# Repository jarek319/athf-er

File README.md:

# athf-er
Blinking LED welcome sign

I made this sign to welcome people to my house warming party. The lights alternate between his hand being down and flying the bird.

I was never comfortable in Inkscape, so I made the acrylic laser cutout design using Eagle. This helped me get exact sizing for the cutouts and an easily mesaureable layout, perfect for pixel stuff.

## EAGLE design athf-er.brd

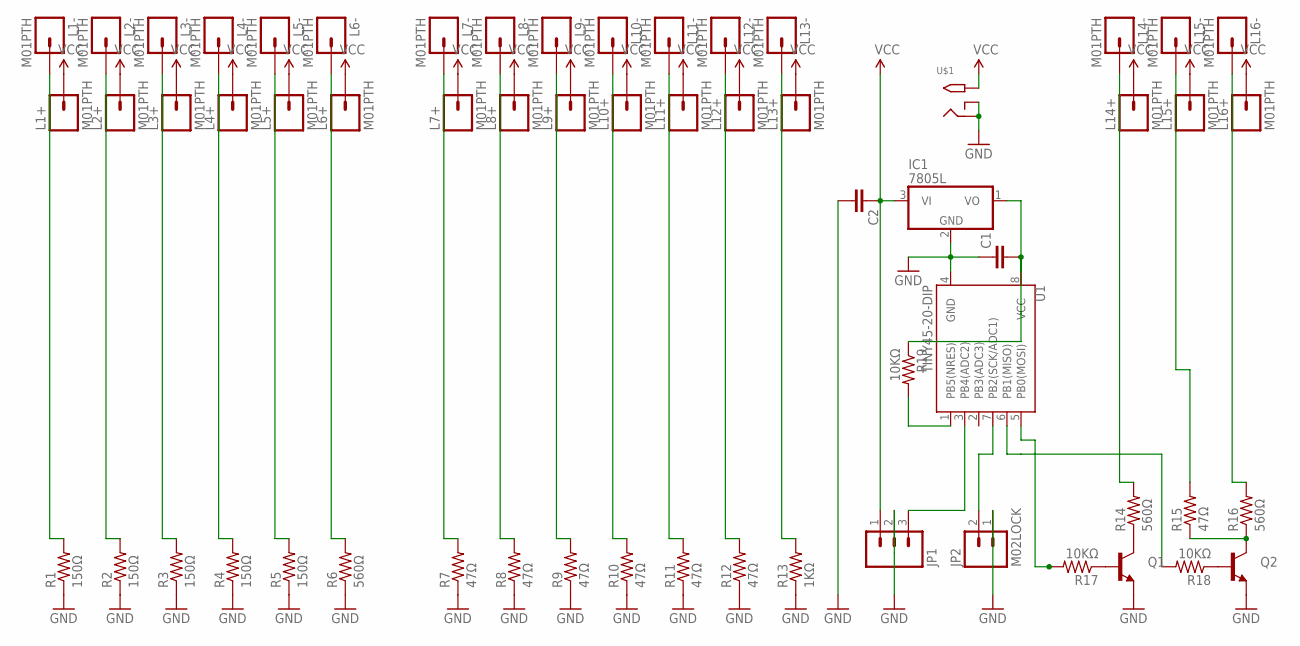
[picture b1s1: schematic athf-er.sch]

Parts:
C1, C2: CAPEZ; CAP-PTH-SMALLEZ
IC1: 7805L; TO92
JP1: M03LOCK; 1X03_LOCK
JP2: M02LOCK; 1X02_LOCK
L1+, L1-, L2+, L2-, L3+, L3-, L4+, L4-, L5+, L5-, L6+, L6-, L7+, L7-, L8+, L8-, L9+, L9-, L10+, L10-, L11+, L11-, L12+, L12-, L13+, L13-, L14+, L14-, L15+, L15-, L16+, L16-: M01PTH; 1X01
Q1, Q2: TRANSISTOR_NPNTO92; TO-92
R1, R2, R3, R4, R5: 150Ω; AXIAL-0.3EZ
R6, R14, R16: 560Ω; AXIAL-0.3EZ
R7, R8, R9, R10, R11, R12, R15: 47Ω; AXIAL-0.3EZ
R13: 1KΩ; AXIAL-0.3EZ
R17, R18, R19: 10KΩ; AXIAL-0.3EZ
U1: TINY45-20-DIP; DIP08
U$1: 2.1MMJACKTHM; PJ-102A

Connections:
GND: C1.1, C2.2, IC1.2 (GND), JP1.2, JP2.1, Q1.1 (E), Q2.1 (E), R1.P$1 (1), R2.P$1 (1), R3.P$1 (1), R4.P$1 (1), R5.P$1 (1), R6.P$1 (1), R7.P$1 (1), R8.P$1 (1), R9.P$1 (1), R10.P$1 (1), R11.P$1 (1), R12.P$1 (1), R13.P$1 (1), U1.4 (GND), U$1.RING, U$1.RING_SW
unnamed: L1-.1, R1.P$2 (2)
unnamed: L2-.1, R2.P$2 (2)
unnamed: L3-.1, R3.P$2 (2)
unnamed: L4-.1, R4.P$2 (2)
unnamed: L5-.1, R5.P$2 (2)
unnamed: L6-.1, R6.P$2 (2)
unnamed: L7-.1, R7.P$2 (2)
unnamed: L8-.1, R8.P$2 (2)
unnamed: L9-.1, R9.P$2 (2)
unnamed: L10-.1, R10.P$2 (2)
unnamed: L11-.1, R11.P$2 (2)
unnamed: L12-.1, R12.P$2 (2)
unnamed: L13-.1, R13.P$2 (2)
unnamed: L14-.1, R14.P$2 (2)
unnamed: L16-.1, R16.P$2 (2)
unnamed: L15-.1, R15.P$2 (2)
unnamed: JP2.2, U1.7 (PB2(SCK/ADC1))
unnamed: Q2.3 (C), R15.P$1 (1), R16.P$1 (1)
unnamed: Q1.2 (B), R17.P$1 (1)
unnamed: Q1.3 (C), R14.P$1 (1)
unnamed: Q2.2 (B), R18.P$1 (1)
unnamed: JP1.3, U1.3 (PB4(ADC2))
unnamed: C1.2, IC1.1 (VO), R19.P$1 (1), U1.8 (VCC)
unnamed: R18.P$2 (2), U1.6 (PB1(MISO))
unnamed: R19.P$2 (2), U1.1 (PB5(NRES))
unnamed: R17.P$2 (2), U1.5 (PB0(MOSI))
VCC: C2.1, IC1.3 (VI), JP1.1, L1+.1, L2+.1, L3+.1, L4+.1, L5+.1, L6+.1, L7+.1, L8+.1, L9+.1, L10+.1, L11+.1, L12+.1, L13+.1, L14+.1, L15+.1, L16+.1, U$1.TIP

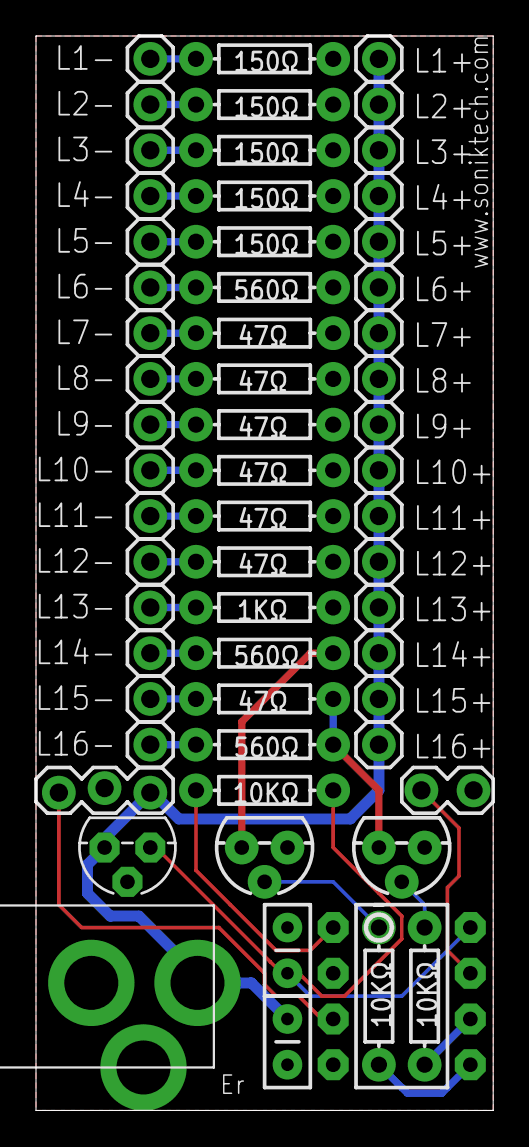
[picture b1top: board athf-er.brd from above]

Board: 2 copper layers, 25.4 x 59.7 mm, 60 parts (0 on the bottom side), 28 nets.

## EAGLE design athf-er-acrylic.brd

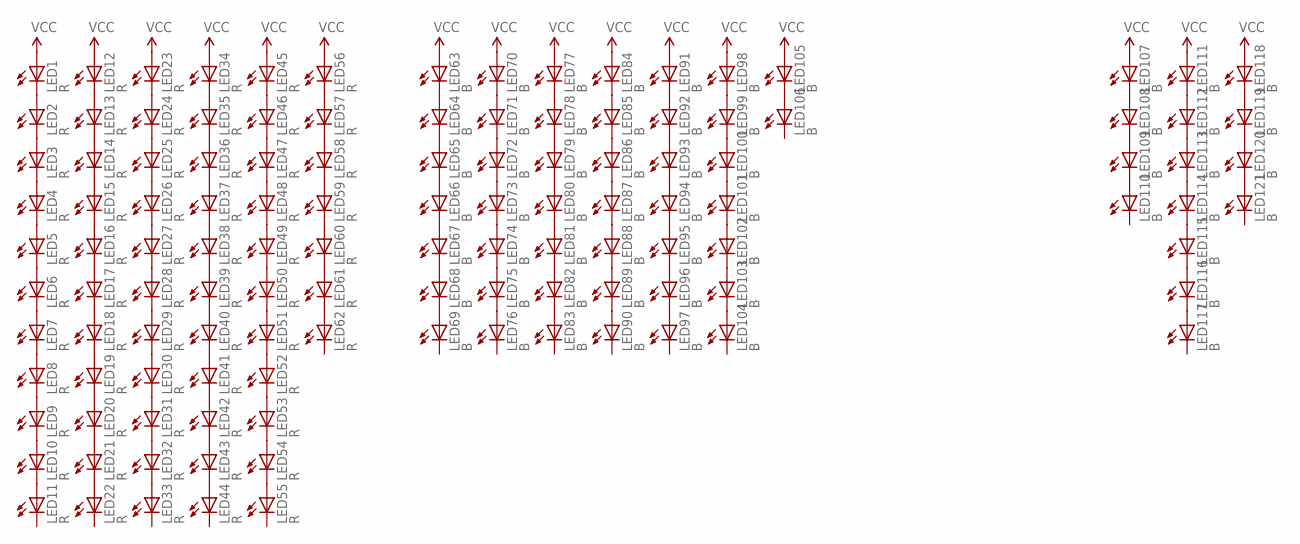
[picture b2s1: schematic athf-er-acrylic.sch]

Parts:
LED1, LED2, LED3, LED4, LED5, LED6, LED7, LED8, LED9, LED10, LED11, LED12, LED13, LED14, LED15, LED16, LED17, LED18, LED19, LED20, LED21, LED22, LED23, LED24, LED25, LED26, LED27, LED28, LED29, LED30, LED31, LED32, LED33, LED34, LED35, LED36, LED37, LED38, LED39, LED40, LED41, LED42, LED43, LED44, LED45, LED46, LED47, LED48, LED49, LED50, LED51, LED52, LED53, LED54, LED55, LED56, LED57, LED58, LED59, LED60, LED61, LED62: R; LED5MMSQUARE
LED63, LED64, LED65, LED66, LED67, LED68, LED69, LED70, LED71, LED72, LED73, LED74, LED75, LED76, LED77, LED78, LED79, LED80, LED81, LED82, LED83, LED84, LED85, LED86, LED87, LED88, LED89, LED90, LED91, LED92, LED93, LED94, LED95, LED96, LED97, LED98, LED99, LED100, LED101, LED102, LED103, LED104, LED105, LED106, LED107, LED108, LED109, LED110, LED111, LED112, LED113, LED114, LED115, LED116, LED117, LED118, LED119, LED120, LED121: B; LED5MMSQUARE

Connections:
unnamed: LED7.K (C), LED8.A
unnamed: LED6.K (C), LED7.A
unnamed: LED13.K (C), LED14.A
unnamed: LED111.K (C), LED112.A
unnamed: LED18.K (C), LED19.A
unnamed: LED107.K (C), LED108.A
unnamed: LED105.K (C), LED106.A
unnamed: LED14.K (C), LED15.A
unnamed: LED15.K (C), LED16.A
unnamed: LED30.K (C), LED31.A
unnamed: LED16.K (C), LED17.A
unnamed: LED36.K (C), LED37.A
unnamed: LED2.K (C), LED3.A
unnamed: LED3.K (C), LED4.A
unnamed: LED108.K (C), LED109.A
unnamed: LED48.K (C), LED49.A
unnamed: LED4.K (C), LED5.A
unnamed: LED1.K (C), LED2.A
unnamed: LED109.K (C), LED110.A
unnamed: LED63.K (C), LED64.A
unnamed: LED60.K (C), LED61.A
unnamed: LED64.K (C), LED65.A
unnamed: LED65.K (C), LED66.A
unnamed: LED66.K (C), LED67.A
unnamed: LED112.K (C), LED113.A
unnamed: LED67.K (C), LED68.A
unnamed: LED68.K (C), LED69.A
unnamed: LED17.K (C), LED18.A
unnamed: LED42.K (C), LED43.A
unnamed: LED54.K (C), LED55.A
unnamed: LED70.K (C), LED71.A
unnamed: LED71.K (C), LED72.A
unnamed: LED72.K (C), LED73.A
unnamed: LED118.K (C), LED119.A
unnamed: LED119.K (C), LED120.A
unnamed: LED73.K (C), LED74.A
unnamed: LED74.K (C), LED75.A
unnamed: LED5.K (C), LED6.A
unnamed: LED8.K (C), LED9.A
unnamed: LED9.K (C), LED10.A
unnamed: LED10.K (C), LED11.A
unnamed: LED12.K (C), LED13.A
unnamed: LED19.K (C), LED20.A
unnamed: LED20.K (C), LED21.A
unnamed: LED21.K (C), LED22.A
unnamed: LED24.K (C), LED25.A
unnamed: LED23.K (C), LED24.A
unnamed: LED25.K (C), LED26.A
unnamed: LED26.K (C), LED27.A
unnamed: LED27.K (C), LED28.A
unnamed: LED28.K (C), LED29.A
unnamed: LED29.K (C), LED30.A
unnamed: LED31.K (C), LED32.A
unnamed: LED32.K (C), LED33.A
unnamed: LED34.K (C), LED35.A
unnamed: LED35.K (C), LED36.A
unnamed: LED37.K (C), LED38.A
unnamed: LED38.K (C), LED39.A
unnamed: LED39.K (C), LED40.A
unnamed: LED40.K (C), LED41.A
unnamed: LED41.K (C), LED42.A
unnamed: LED43.K (C), LED44.A
unnamed: LED45.K (C), LED46.A
unnamed: LED46.K (C), LED47.A
unnamed: LED47.K (C), LED48.A
unnamed: LED49.K (C), LED50.A
unnamed: LED50.K (C), LED51.A
unnamed: LED51.K (C), LED52.A
unnamed: LED52.K (C), LED53.A
unnamed: LED53.K (C), LED54.A
unnamed: LED56.K (C), LED57.A
unnamed: LED57.K (C), LED58.A
unnamed: LED58.K (C), LED59.A
unnamed: LED59.K (C), LED60.A
unnamed: LED61.K (C), LED62.A
unnamed: LED75.K (C), LED76.A
unnamed: LED77.K (C), LED78.A
unnamed: LED78.K (C), LED79.A
unnamed: LED79.K (C), LED80.A
unnamed: LED80.K (C), LED81.A
unnamed: LED81.K (C), LED82.A
unnamed: LED82.K (C), LED83.A
unnamed: LED84.K (C), LED85.A
unnamed: LED85.K (C), LED86.A
unnamed: LED86.K (C), LED87.A
unnamed: LED87.K (C), LED88.A
unnamed: LED88.K (C), LED89.A
unnamed: LED89.K (C), LED90.A
unnamed: LED91.K (C), LED92.A
unnamed: LED92.K (C), LED93.A
unnamed: LED93.K (C), LED94.A
unnamed: LED94.K (C), LED95.A
unnamed: LED95.K (C), LED96.A
unnamed: LED96.K (C), LED97.A
unnamed: LED98.K (C), LED99.A
unnamed: LED99.K (C), LED100.A
unnamed: LED100.K (C), LED101.A
unnamed: LED101.K (C), LED102.A
unnamed: LED102.K (C), LED103.A
unnamed: LED103.K (C), LED104.A
unnamed: LED113.K (C), LED114.A
unnamed: LED114.K (C), LED115.A
unnamed: LED115.K (C), LED116.A
unnamed: LED116.K (C), LED117.A
unnamed: LED120.K (C), LED121.A
VCC: LED1.A, LED12.A, LED23.A, LED34.A, LED45.A, LED56.A, LED63.A, LED70.A, LED77.A, LED84.A, LED91.A, LED98.A, LED105.A, LED107.A, LED111.A, LED118.A

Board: 2 copper layers, 121 parts (0 on the bottom side), 106 nets, no tracks yet.

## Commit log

2018-07-04 design tested: working

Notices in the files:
parts and their libraries:
SparkFun-Aesthetics: Licensing: CC v3.0 Share-Alike You are welcome to use this library for commercial purposes.
